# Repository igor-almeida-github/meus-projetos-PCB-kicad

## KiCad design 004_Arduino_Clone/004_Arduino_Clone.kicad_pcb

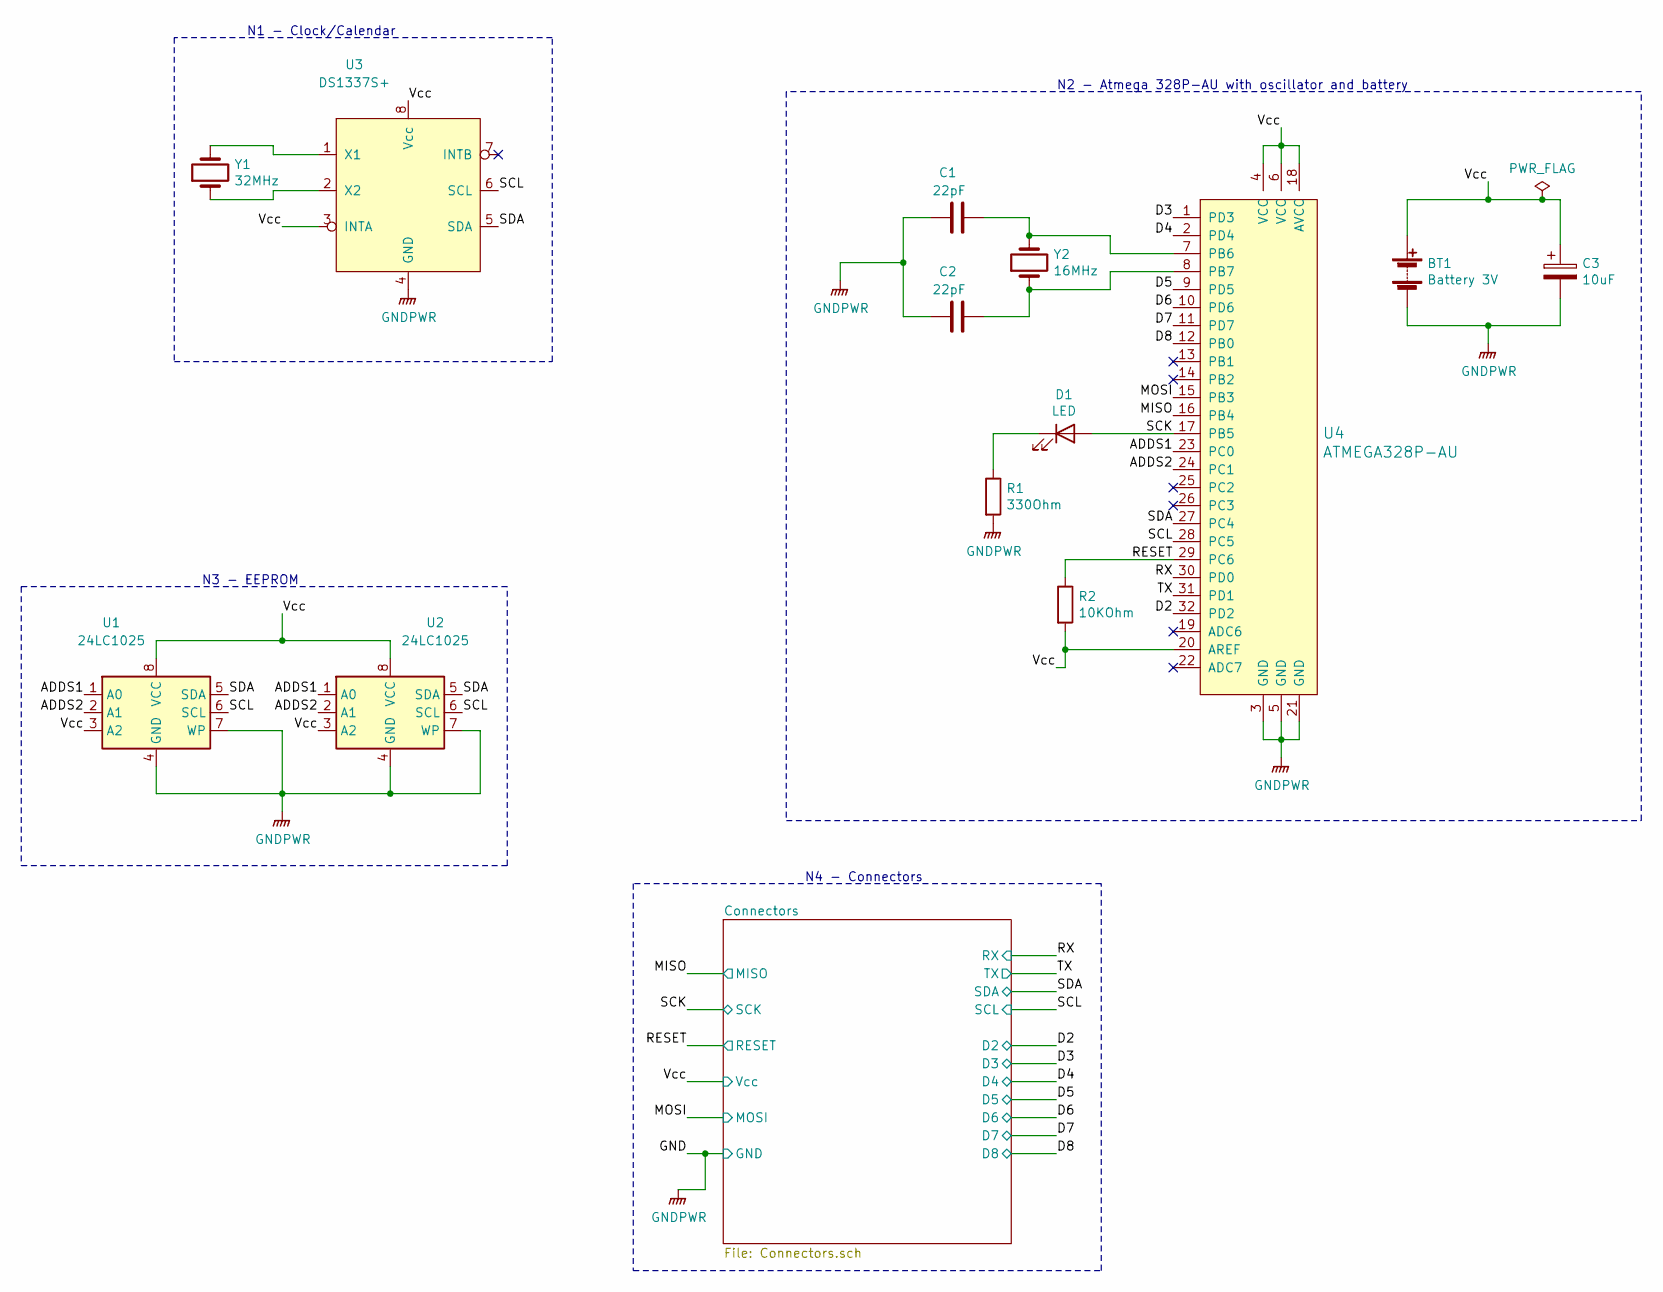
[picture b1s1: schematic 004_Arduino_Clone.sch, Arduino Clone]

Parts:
BT1: Battery 3V; PinHeader_1x02_P2.54mm_Vertical
C1, C2: 22pF; C_0805_2012Metric_Pad1.18x1.45mm_HandSolder
C3: 10uF; C_0805_2012Metric_Pad1.18x1.45mm_HandSolder
D1: LED; LED_0805_2012Metric_Pad1.15x1.40mm_HandSolder
R1: 330Ohm; R_0805_2012Metric_Pad1.20x1.40mm_HandSolder
R2: 10KOhm; R_0805_2012Metric_Pad1.20x1.40mm_HandSolder
U1, U2: 24LC1025; SOIJ-8_5.3x5.3mm_P1.27mm
U3: DS1337S+; SO-8_5.3x6.2mm_P1.27mm
U4: ATMEGA328P-AU; TQFP-32_7x7mm; MPN ATMEGA328P-AU; Digi-Key_PN ATMEGA328P-AU-ND
Y1: 32MHz; Crystal_SMD_MicroCrystal_CC7V-T1A-2Pin_3.2x1.5mm
Y2: 16MHz; Crystal_SMD_5032-2Pin_5.0x3.2mm

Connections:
/ADDS1: U1.1 (A0), U2.1 (A0), U4.23 (PC0)
/ADDS2: U1.2 (A1), U2.2 (A1), U4.24 (PC1)
/D2: U4.32 (PD2); also elsewhere on the board
/D3: U4.1 (PD3); also elsewhere on the board
/D4: U4.2 (PD4); also elsewhere on the board
/D5: U4.9 (PD5); also elsewhere on the board
/D6: U4.10 (PD6); also elsewhere on the board
/D7: U4.11 (PD7); also elsewhere on the board
/D8: U4.12 (PB0); also elsewhere on the board
/MISO: U4.16 (PB4); also elsewhere on the board
/MOSI: U4.15 (PB3); also elsewhere on the board
/RESET: R2.1, U4.29 (PC6); also elsewhere on the board
/RX: U4.30 (PD0); also elsewhere on the board
/SCK: D1.2 (A), U4.17 (PB5); also elsewhere on the board
/SCL: U1.6 (SCL), U2.6 (SCL), U3.6 (SCL), U4.28 (PC5); also elsewhere on the board
/SDA: U1.5 (SDA), U2.5 (SDA), U3.5 (SDA), U4.27 (PC4); also elsewhere on the board
/TX: U4.31 (PD1); also elsewhere on the board
/Vcc: BT1.1 (+), C3.1, R2.2, U1.3 (A2), U1.8 (VCC), U2.3 (A2), U2.8 (VCC), U3.3 (INTA), U3.8 (Vcc), U4.4 (VCC), U4.6 (VCC), U4.18 (AVCC), U4.20 (AREF); also elsewhere on the board
GNDPWR: BT1.2 (-), C1.1, C2.1, C3.2, R1.2, U1.4 (GND), U1.7 (WP), U2.4 (GND), U2.7 (WP), U3.4 (GND), U4.3 (GND), U4.5 (GND), U4.21 (GND); also elsewhere on the board
unnamed: C1.2, U4.7 (PB6), Y2.2
unnamed: C2.2, U4.8 (PB7), Y2.1
unnamed: D1.1 (K), R1.1
unnamed: U3.1 (X1), Y1.2
unnamed: U3.2 (X2), Y1.1

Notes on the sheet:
N1 - Clock/Calendar
N3 - EEPROM
N2 - Atmega 328P-AU with oscillator and battery
N4 - Connectors

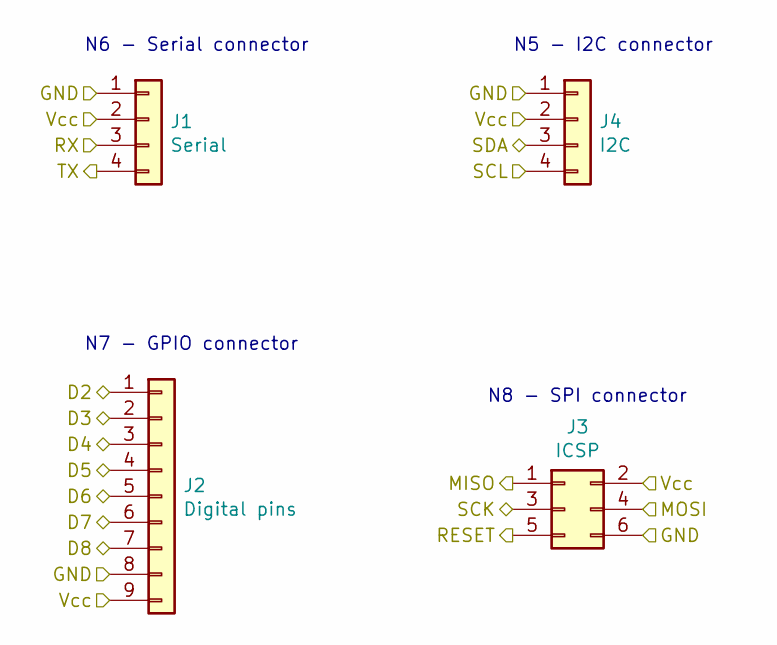
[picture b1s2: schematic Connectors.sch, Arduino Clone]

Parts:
J1: Serial; PinSocket_1x04_P2.54mm_Vertical
J2: Digital pins; PinSocket_1x09_P2.54mm_Vertical
J3: ICSP; PinSocket_2x03_P2.54mm_Vertical
J4: I2C; PinSocket_1x04_P2.54mm_Vertical

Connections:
/D2: J2.1; also elsewhere on the board
/D3: J2.2; also elsewhere on the board
/D4: J2.3; also elsewhere on the board
/D5: J2.4; also elsewhere on the board
/D6: J2.5; also elsewhere on the board
/D7: J2.6; also elsewhere on the board
/D8: J2.7; also elsewhere on the board
/MISO: J3.1; also elsewhere on the board
/MOSI: J3.4; also elsewhere on the board
/RESET: J3.5; also elsewhere on the board
/RX: J1.3; also elsewhere on the board
/SCK: J3.3; also elsewhere on the board
/SCL: J4.4; also elsewhere on the board
/SDA: J4.3; also elsewhere on the board
/TX: J1.4; also elsewhere on the board
/Vcc: J1.2, J2.9, J3.2, J4.2; also elsewhere on the board
GNDPWR: J1.1, J2.8, J3.6, J4.1; also elsewhere on the board

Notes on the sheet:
N6 - Serial connector
N5 - I2C connector
N7 - GPIO connector
N8 - SPI connector

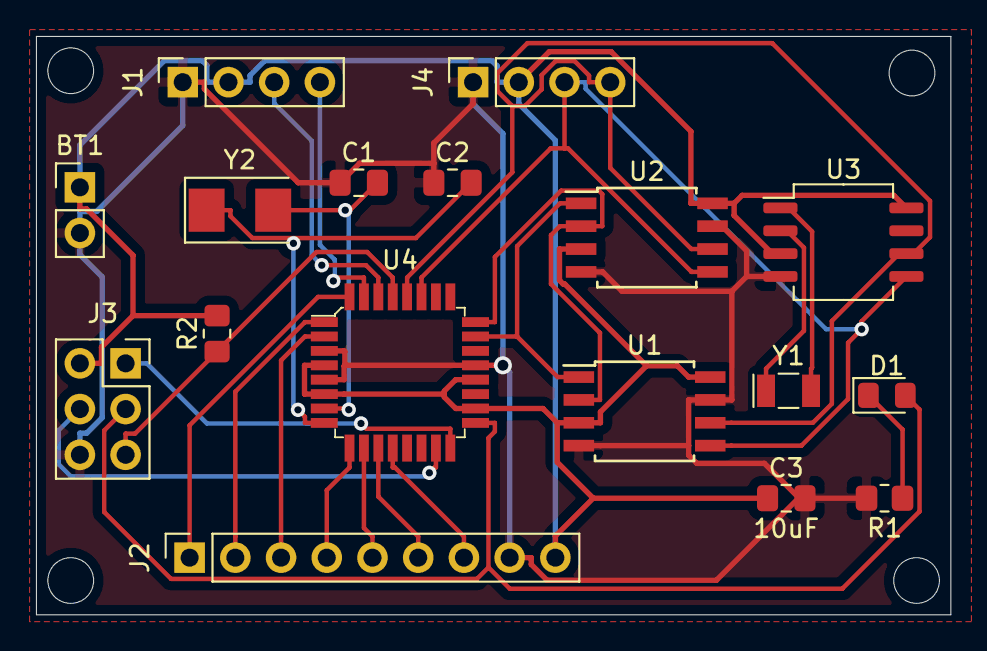
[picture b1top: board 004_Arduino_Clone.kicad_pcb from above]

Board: 2 copper layers, 50.8 x 32.1 mm, 17 parts (0 on the bottom side), 24 nets.

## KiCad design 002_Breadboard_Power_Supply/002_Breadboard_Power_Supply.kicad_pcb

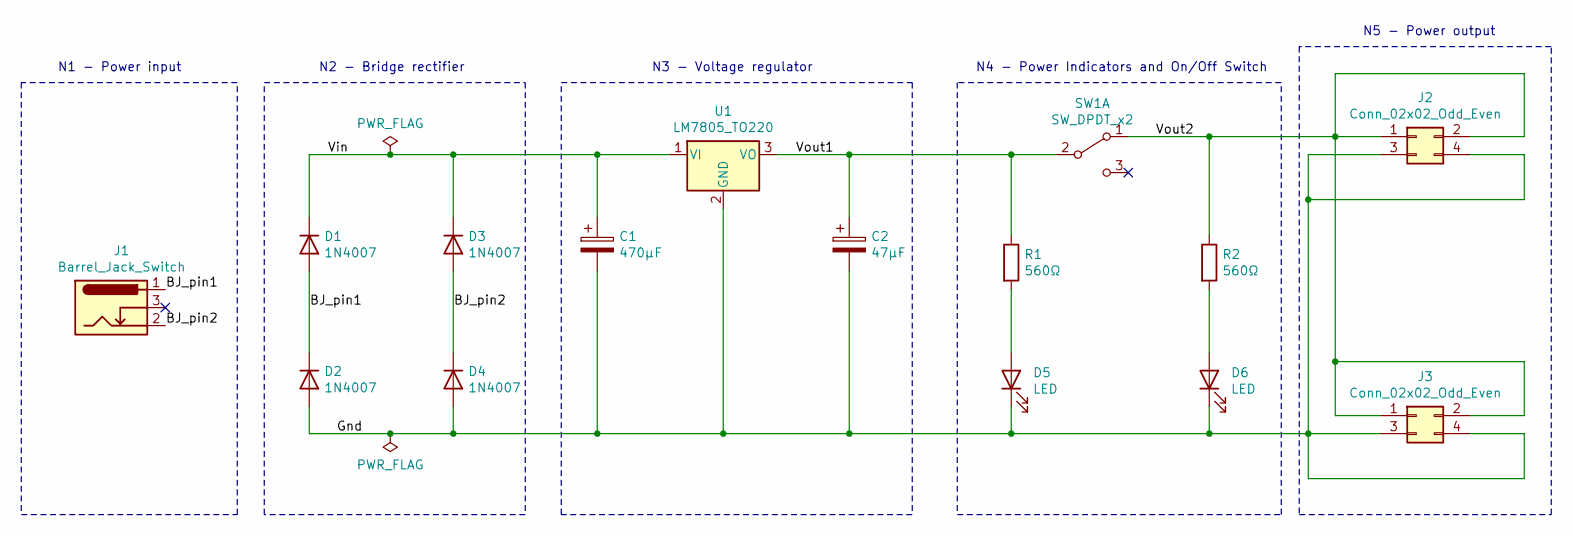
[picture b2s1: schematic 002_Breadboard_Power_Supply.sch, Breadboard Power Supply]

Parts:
C1: 470μF; CP_Radial_D10.0mm_P5.00mm
C2: 47μF; CP_Radial_D6.3mm_P2.50mm
D1, D2, D3, D4: 1N4007; D_DO-41_SOD81_P10.16mm_Horizontal
D5, D6: LED; LED_D5.0mm
J1: Barrel_Jack_Switch; BarrelJack_CUI_PJ-102AH_Horizontal
J2, J3: Conn_02x02_Odd_Even; PinHeader_2x02_P2.54mm_Vertical
R1, R2: 560Ω; R_Axial_DIN0207_L6.3mm_D2.5mm_P7.62mm_Horizontal
SW1: SW_DPDT_x2; Switch_Slide_11.6x4mm_EG1218
U1: LM7805_TO220; TO-220-3_Vertical

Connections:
/BJ_pin1: D1.2 (A), D2.1 (K), J1.1
/BJ_pin2: D3.2 (A), D4.1 (K), J1.2
/Gnd: C1.2, C2.2, D2.2 (A), D4.2 (A), D5.1 (K), D6.1 (K), J2.3, J2.4, J3.3, J3.4, U1.2 (GND)
/Vin: C1.1, D1.1 (K), D3.1 (K), U1.1 (VI)
/Vout1: C2.1, R1.1, SW1.2 (B), U1.3 (VO)
/Vout2: J2.1, J2.2, J3.1, J3.2, R2.1, SW1.1 (A)
unnamed: D5.2 (A), R1.2
unnamed: D6.2 (A), R2.2

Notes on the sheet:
N1 - Power input
N2 - Bridge rectifier
N3 - Voltage regulator
N4 - Power Indicators and On/Off Switch
N5 - Power output

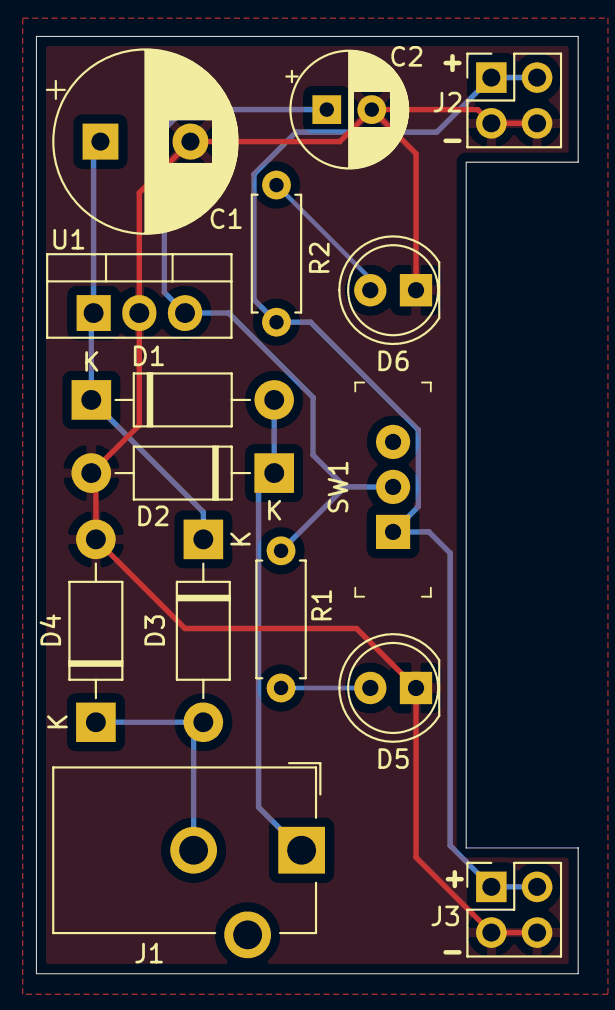
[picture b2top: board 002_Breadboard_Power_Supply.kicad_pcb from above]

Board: 2 copper layers, 30.1 x 52.1 mm, 15 parts (0 on the bottom side), 8 nets.

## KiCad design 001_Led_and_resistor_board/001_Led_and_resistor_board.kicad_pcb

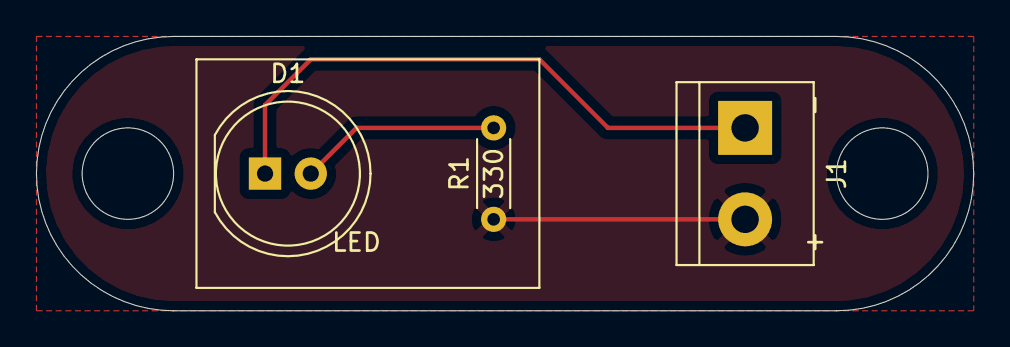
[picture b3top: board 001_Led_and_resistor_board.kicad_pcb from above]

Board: 2 copper layers, 52.1 x 15.2 mm, 3 parts (0 on the bottom side), 3 nets.

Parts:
D1: LED; LED_D8.0mm
J1: Conn_01x02_Male; TerminalBlock_bornier-2_P5.08mm
R1: R; R_Axial_DIN0204_L3.6mm_D1.6mm_P5.08mm_Horizontal

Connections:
+5V: J1.2, R1.1
GND: D1.1, J1.1
unnamed: D1.2, R1.2

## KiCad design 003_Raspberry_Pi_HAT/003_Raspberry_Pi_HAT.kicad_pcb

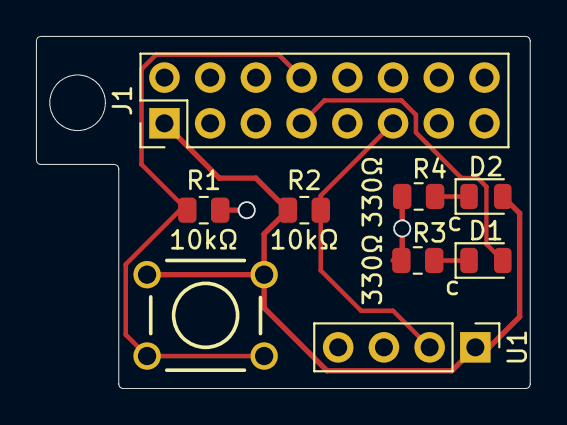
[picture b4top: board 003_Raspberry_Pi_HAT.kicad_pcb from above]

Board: 2 copper layers, 27.4 x 19.6 mm, 9 parts (0 on the bottom side), 7 nets.

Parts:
D1, D2: LED; LED_0805_2012Metric
J1: Raspberry_Pi_2_3; PinHeader_2x08_P2.54mm_Vertical
R1, R2: 10kΩ; R_0805_2012Metric
R3, R4: 330Ω; R_0805_2012Metric
SW1: SW_DPST; SW_PUSHBUTTON_PTH
U1: DHT22; PinHeader_1x04_P2.54mm_Vertical

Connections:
/3V3: D2.2, J1.1, R2.1, SW1.1, U1.1
/button_in: J1.8, R1.1, SW1.2
GND: J1.6, J1.9, R1.2, R3.2, R4.2, U1.4
unnamed: D1.1, R3.1
unnamed: D1.2, J1.7
unnamed: D2.1, R4.1
unnamed: J1.11, R2.2, U1.2

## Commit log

2021-09-12 Arduivos adicionados
